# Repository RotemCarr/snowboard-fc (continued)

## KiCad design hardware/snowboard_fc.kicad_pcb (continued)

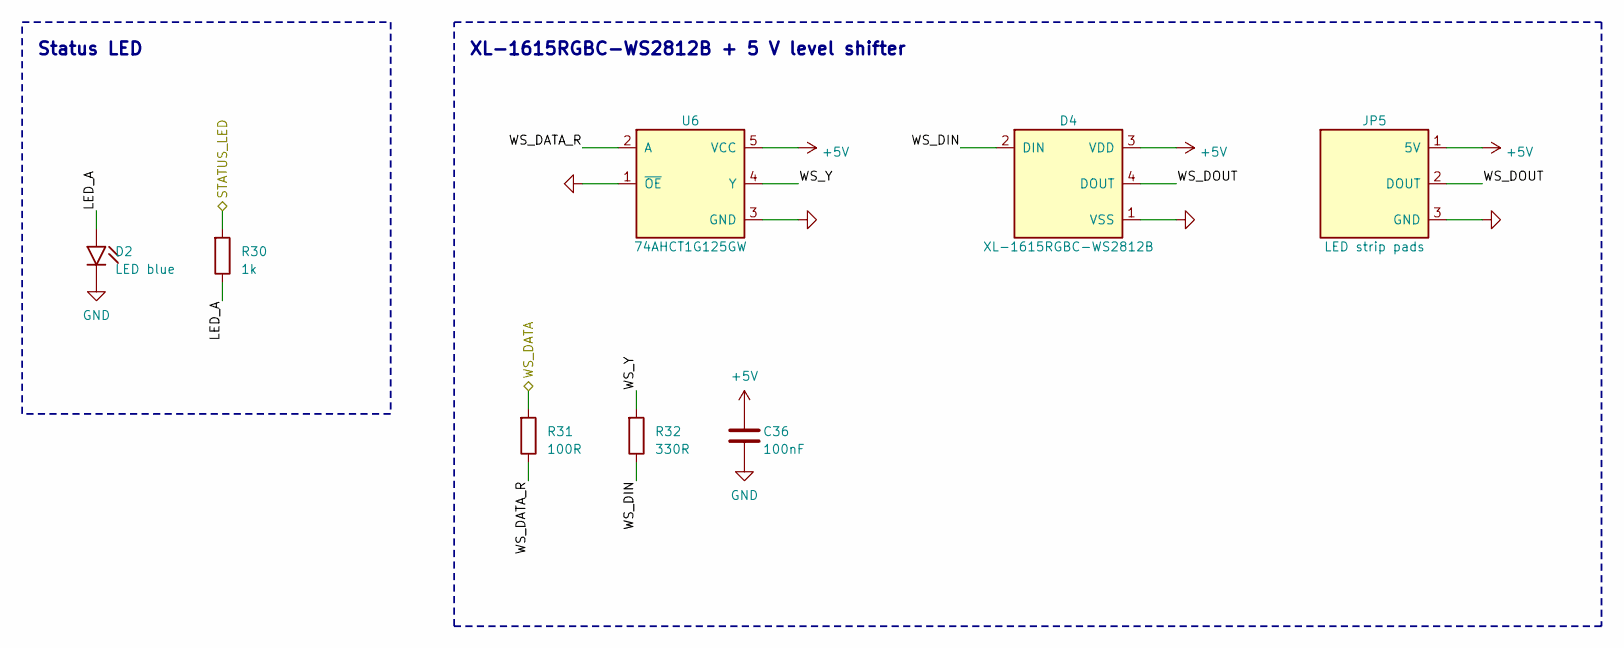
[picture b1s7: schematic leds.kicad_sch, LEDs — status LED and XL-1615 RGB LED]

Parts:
C36: 100nF; C_0402_1005Metric; LCSC C1525
D2: LED blue; LED_0603_1608Metric; LCSC C125096
D4: XL-1615RGBC-WS2812B; LED_XL-1615RGBC-WS2812B; MPN XL-1615RGBC-WS2812B (XINGLIGHT); LCSC C5349954
JP5: LED strip pads; PinHeader_1x03_P1.27mm_Vertical
R30: 1k; R_0402_1005Metric; LCSC C11702
R31: 100R; R_0402_1005Metric; LCSC C25076
R32: 330R; R_0402_1005Metric; LCSC C25104
U6: 74AHCT1G125GW; SOT-353_SC-70-5; MPN 74AHCT1G125GW (Nexperia); LCSC C52953352

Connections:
+5V: C36.1, D4.3 (VDD), JP5.1 (5V), U6.5 (VCC); also elsewhere on the board
/LEDs/LED_A: D2.2, R30.2
/LEDs/WS_DATA_R: R31.2, U6.2 (A)
/LEDs/WS_DIN: D4.2 (DIN), R32.2
/LEDs/WS_DOUT: D4.4 (DOUT), JP5.2 (DOUT)
/LEDs/WS_Y: R32.1, U6.4 (Y)
/STATUS_LED: R30.1; also elsewhere on the board
/WS_DATA: R31.1; also elsewhere on the board
GND: C36.2, D2.1, D4.1 (VSS), JP5.3 (GND), U6.1 (~OE), U6.3 (GND); also elsewhere on the board

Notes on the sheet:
Status LED
XL-1615RGBC-WS2812B + 5 V level shifter

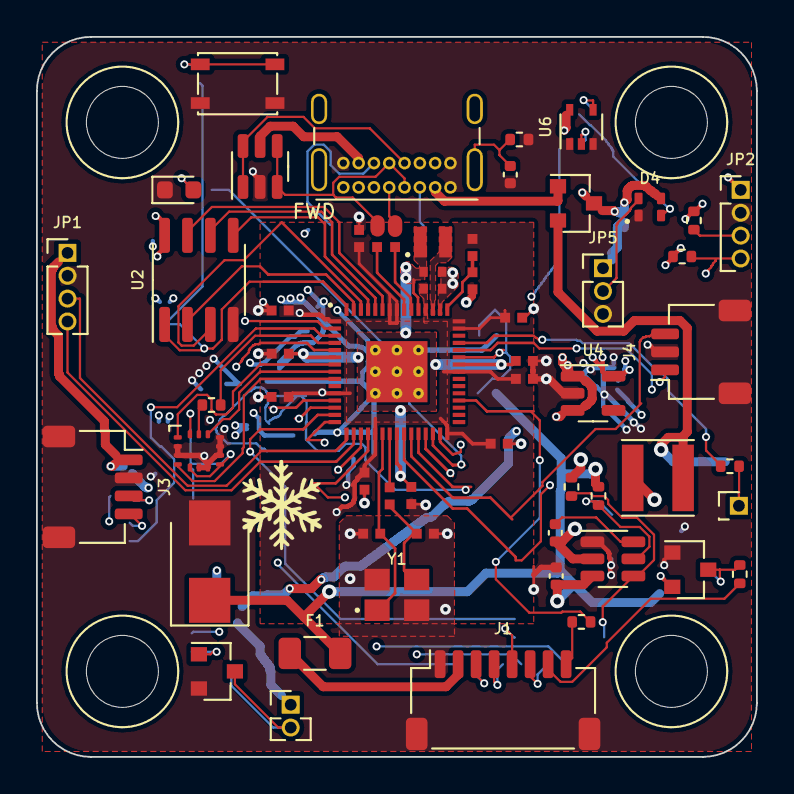
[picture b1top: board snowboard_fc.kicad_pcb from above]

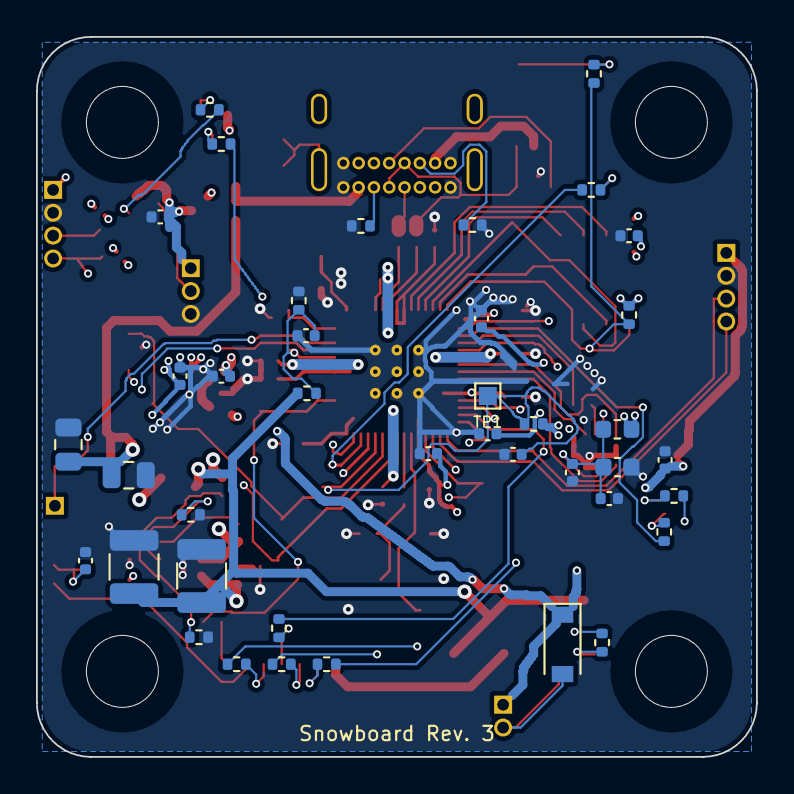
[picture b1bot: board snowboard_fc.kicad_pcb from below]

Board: 4 copper layers, 40.0 x 40.0 mm, 102 parts (40 on the bottom side), 74 nets.

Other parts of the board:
H1, H2, H3, H4: M3 grommet 4.0mm; MountingHole_4.0mm_Grommet

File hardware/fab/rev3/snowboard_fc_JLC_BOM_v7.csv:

Comment,Designator,Footprint,LCSC Part #
4.7uF 10V X5R,"C1,C4,C5",0402,C23733
100nF 16V X7R,"C2,C3,C6,C7,C8,C9,C10,C11,C12,C13,C14,C16,C17,C20,C24,C30,C33,C34,C35,C36",0402,C1525
1uF 25V X5R,"C15,C27,C28",0402,C52923
15pF 50V C0G,"C18,C19",0402,C1548
10uF 100V X7R,"C21,C22",1210,C5156756
100nF 50V X7R,C23,0402,C307331
22uF 25V X5R,"C25,C26",0805,C45783
2.2uF 16V X5R,C29,0603,C23630
10nF 50V X7R,C31,0402,C696350
4.7nF 50V X7R,C32,0402,C1538
BAT54C,D1,SOT-23,C22466350
LED blue 0603,D2,0603,C125096
SMBJ26A,D3,SMB,C3019963
XINGLIGHT XL-1615RGBC-WS2812B,D4,1615,C5349954
USBLC6-2SC6,D5,SOT-23-6,C7519
BAT54S,D6,SOT-23,C7420333
1N4148W,D7,SOD-123,C81598
F12F1 fuse 1A fast 1206 32V,F1,1206,C2924985
600R@100MHz ferrite,FB1,0603,C1002
JST SM08B-SRSS-TB(LF)(SN) 8-pin SH side entry,J1,SH-1.0mm-8P-RA,C160407
GCT USB4085-GF-A USB-C 2.0 (through-hole) - Global Sourcing,J2,USB-C THT,
JST SM04B-SRSS-TB(LF)(SN) 4-pin SH side entry,J3,SH-1.0mm-4P-RA,C160404
JST SM03B-SRSS-TB(LF)(SN) 3-pin SH side entry,J4,SH-1.0mm-3P-RA,C160403
10uH 4x4mm shielded,L1,4x4mm,C340371
AOTA-B201610S3R3-101-T 3.3uH (RP2350 recommended),L2,0806,C42411119
2N7002,Q1,SOT-23,C8545
33R 1% 0402,"R1,R10",0402,C25105
10k 1% 0402,"R2,R4,R22,R23,R28",0402,C25744
1k 1% 0402,"R3,R5,R20,R29,R30",0402,C11702
100k 1% 0402,"R6,R8,R21",0402,C25741
20k 1% 0402,R7,0402,C25765
13.3k 1% 0402,R9,0402,C122547
5.1k 1% 0402,"R11,R12",0402,C25905
1M 1% 0402,R13,0402,C26083
27R 1% 0402,"R14,R15",0402,C25100
100R 1% 0402,"R16,R17,R18,R19,R24,R25,R31",0402,C25076
4.7k 1% 0402,"R26,R27",0402,C25900
330R 1% 0402,R32,0402,C25104
C&K PTS810SJM250SMTRLFS tactile switch - Global Sourcing,SW1,SMD,
RP2350A,U1,QFN-60,C42411118
W25Q32JVSNIQ,U2,SOIC-8,C5355146
TPS54202DDCT,U3,SOT-23-6,C2070672
AP2112K-3.3TRG1,U4,SOT-23-5,C51118
ICM-42688-P,U5,LGA-14,C1850418
74AHCT1G125GW,U6,SOT-353,C52953352
ABM8-272-T3 12MHz 10pF (RP2350 recommended),Y1,3225,C20625731

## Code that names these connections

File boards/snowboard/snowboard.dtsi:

/*
 * Snowboard Rev 3 board-level devicetree.
 * Source: hardware/docs/pinmap.md, SNB-HW-001.
 *
 * TODO: flash partitions and retained RAM (RFC 0002 sections 8 and 9.4).
 * TODO: DShot on &pio0 once the custom binding exists.
 * TODO: CRSF receiver node on &uart0 once the driver exists.
 *
 * SPDX-License-Identifier: Apache-2.0
 */

#include <freq.h>

#include <zephyr/dt-bindings/adc/adc.h>
#include <zephyr/dt-bindings/i2c/i2c.h>
#include <zephyr/dt-bindings/led/led.h>
#include <zephyr/dt-bindings/sensor/icm42688.h>

#include "snowboard-pinctrl.dtsi"

/ {
	model = "Snowboard flight controller";
	compatible = "snowboard,snowboard-fc";

	chosen {
		zephyr,sram = &sram0;
		zephyr,flash = &flash0;
		zephyr,flash-controller = &qmi;
	};

	aliases {
		led0 = &status_led;
		led-strip = &rgb_led;
		buzzer = &buzzer;
		watchdog0 = &wdt0;
	};

	leds {
		compatible = "gpio-leds";

		/* D2, blue, through 1 kOhm */
		status_led: status_led {
			gpios = <&gpio0 17 GPIO_ACTIVE_HIGH>;
			label = "Status LED";
		};
	};

	buzzer {
		compatible = "gpio-leds";

		/* Low-side driver Q1; BZ+ on 5 V */
		buzzer: buzzer {
			gpios = <&gpio0 18 GPIO_ACTIVE_HIGH>;
			label = "Buzzer";
		};
	};

	/* VBAT = J1 pin 2 through R21 100k / R22 10k (divide by 11) */
	vbat: vbat {
		compatible = "voltage-divider";
		io-channels = <&adc 0>;
		output-ohms = <10000>;
		full-ohms = <110000>;
	};
};

/* W25Q32JVSNIQ, 4 MB. */
&flash0 {
	reg = <0x10000000 DT_SIZE_M(4)>;
};

/* CRSF receiver on J3 */
&uart0 {
	current-speed = <420000>;
	status = "okay";
	pinctrl-0 = <&uart0_default>;
	pinctrl-names = "default";
};

&gpio0 {
	status = "okay";
};

&spi0 {
	pinctrl-0 = <&spi0_default>;
	pinctrl-names = "default";
	clock-frequency = <DT_FREQ_M(24)>;
	cs-gpios = <&gpio0 5 GPIO_ACTIVE_LOW>;
	status = "okay";

	imu: icm42688@0 {
		compatible = "invensense,icm42688", "invensense,icm4268x";
		reg = <0>;
		spi-max-frequency = <DT_FREQ_M(24)>;
		/* INT1: push-pull, no pull-up on the board; driver default is active high */
		int-gpios = <&gpio0 6 GPIO_ACTIVE_HIGH>;
		gyro-pwr-mode = <ICM42688_DT_GYRO_LN>;
		gyro-fs = <ICM42688_DT_GYRO_FS_2000>;
		gyro-odr = <ICM42688_DT_GYRO_ODR_8000>;
		accel-pwr-mode = <ICM42688_DT_ACCEL_LN>;
		accel-fs = <ICM42688_DT_ACCEL_FS_16>;
		accel-odr = <ICM42688_DT_ACCEL_ODR_8000>;
	};
};

/* Aux I2C pads (JP2), nothing fitted */
&i2c1 {
	clock-frequency = <I2C_BITRATE_STANDARD>;
	pinctrl-0 = <&i2c1_default>;
	pinctrl-names = "default";
	status = "disabled";
};

&adc {
	pinctrl-0 = <&adc_default>;
	pinctrl-names = "default";
	#address-cells = <1>;
	#size-cells = <0>;
	status = "okay";

	/* VBAT_SENSE, GPIO26 */
	channel@0 {
		reg = <0>;
		zephyr,gain = "ADC_GAIN_1";
		zephyr,reference = "ADC_REF_INTERNAL";
		zephyr,acquisition-time = <ADC_ACQ_TIME_DEFAULT>;
		zephyr,resolution = <12>;
	};

	/* CUR_SENSE, GPIO27; ESC output 40 mV/A */
	channel@1 {
		reg = <1>;
		zephyr,gain = "ADC_GAIN_1";
		zephyr,reference = "ADC_REF_INTERNAL";
		zephyr,acquisition-time = <ADC_ACQ_TIME_DEFAULT>;
		zephyr,resolution = <12>;
	};

	/* RSSI pad, GPIO28 */
	channel@2 {
		reg = <2>;
		zephyr,gain = "ADC_GAIN_1";
		zephyr,reference = "ADC_REF_INTERNAL";
		zephyr,acquisition-time = <ADC_ACQ_TIME_DEFAULT>;
		zephyr,resolution = <12>;
	};
};

/* PIO0: DShot M1-M4 (GPIO8-11). Enabled with the DShot node. */
&pio0 {
	status = "disabled";
};

/* PIO1: RGB LED D4 via the 74AHCT1G125 level shifter */
&pio1 {
	status = "okay";

	pio-ws2812 {
		compatible = "worldsemi,ws2812-rpi_pico-pio";
		pinctrl-0 = <&pio1_default>;
		pinctrl-names = "default";
		bit-waveform = <3>, <3>, <4>;

		rgb_led: ws2812 {
			gpios = <&gpio0 16 GPIO_ACTIVE_HIGH>;
			chain-length = <1>;
			color-mapping = <LED_COLOR_ID_GREEN LED_COLOR_ID_RED LED_COLOR_ID_BLUE>;
			reset-delay = <300>;
			frequency = <800000>;
		};
	};
};

/* PIO2: aux UART on JP1 (GPIO12/13 have no free hardware UART) */
&pio2 {
	status = "okay";

	aux_uart: uart-aux {
		compatible = "raspberrypi,pico-uart-pio";
		pinctrl-0 = <&pio2_uart_aux_default>;
		pinctrl-names = "default";
		current-speed = <115200>;
	};
};

&timer0 {
	status = "okay";
};

&wdt0 {
	status = "okay";
};

&rng {
	status = "okay";
};

zephyr_udc0: &usbd {
	status = "okay";
};

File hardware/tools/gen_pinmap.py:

#!/usr/bin/env python3
"""Generate docs/pinmap.md from the schematic netlist.

Usage (from the KiCad project directory):
    python3 tools/gen_pinmap.py

Exports the netlist with kicad-cli, maps every RP2350A (U1) pin to its net,
and traces each GPIO through series parts to its far end (connector, pad or
IC). The peripheral column is the firmware's intended pin function, taken
from PERIPHERAL below. The script fails if a GPIO's net no longer matches
EXPECTED_NET, so a schematic change cannot silently desync the firmware DTS.
"""
import re, subprocess, sys, tempfile, pathlib

SCH = "snowboard_fc.kicad_sch"
OUT = pathlib.Path("docs/pinmap.md")
MCU = "U1"

# GPIO -> (expected net, intended peripheral, direction). Keep in sync with
# SNB-HW-001 section 7 and the board DTS.
EXPECTED = {
    0:  ("/RX_TX",      "UART0 TX",        "out"),
    1:  ("/RX_RX",      "UART0 RX",        "in"),
    2:  ("/IMU_SCK",    "SPI0 SCK",        "out"),
    3:  ("/IMU_MOSI",   "SPI0 TX",         "out"),
    4:  ("/IMU_MISO",   "SPI0 RX",         "in"),
    5:  ("/IMU_CS",     "GPIO (SPI0 CS)",  "out"),
    6:  ("/IMU_INT1",   "GPIO interrupt",  "in"),
    8:  ("/M1",         "PIO0 (DShot)",    "out"),
    9:  ("/M2",         "PIO0 (DShot)",    "out"),
    10: ("/M3",         "PIO0 (DShot)",    "out"),
    11: ("/M4",         "PIO0 (DShot)",    "out"),
    12: ("/AUX_TX",     "PIO UART TX",     "out"),
    13: ("/AUX_RX",     "PIO UART RX",     "in"),
    14: ("/I2C_SDA",    "I2C1 SDA",        "bidir"),
    15: ("/I2C_SCL",    "I2C1 SCL",        "out"),
    16: ("/WS_DATA",    "PIO1 (WS2812)",   "out"),
    17: ("/STATUS_LED", "GPIO",            "out"),
    18: ("/BUZZ",       "GPIO",            "out"),
    22: ("/ESC_TEL",    "PIO UART RX",     "in"),
    26: ("/VBAT_SENSE", "ADC0",            "in"),
    27: ("/CUR_SENSE",  "ADC1",            "in"),
    28: ("/RSSI",       "ADC2",            "in"),
}
SERIES = ("R", "L", "FB")      # parts traced through to the far end
RAILS = {"GND", "+3V3", "+5V"}


def export_netlist():
    tmp = pathlib.Path(tempfile.mkdtemp()) / "pinmap.net"
    subprocess.run(["kicad-cli", "sch", "export", "netlist", "--format",
                    "kicadsexpr", "-o", str(tmp), SCH],
                   check=True, capture_output=True)
    return tmp.read_text()


def parse(t):
    values = dict(re.findall(r'\(comp \(ref "([^"]+)"\)\s*\(value "([^"]*)"\)', t))
    nets, net_of, func_of = {}, {}, {}
    for m in re.finditer(r'\(net \(code "?\d+"?\) \(name "([^"]*)"\)(.*?)(?=\(net \(code|\Z)', t, re.S):
        nodes = re.findall(r'\(node \(ref "([^"]+)"\) \(pin "([^"]+)"\)(?: \(pinfunction "([^"]*)"\))?', m.group(2))
        nets[m.group(1)] = nodes
        for r, p, f in nodes:
            net_of[(r, p)] = m.group(1)
            func_of[(r, p)] = f
    return values, nets, net_of, func_of


def pin_order(label):
    m = re.search(r"\((\d+)\)$", label)
    return int(m.group(1)) if m else 999


def fmt(ref, pin, func, values):
    label = f"{ref}.{pin}" + (f" ({func})" if func else "")
    return f"{label} {values.get(ref, '')}".strip()


def trace(net, frm, values, nets, net_of):
    """Describe where a net goes, following 2-pin series parts once."""
    out = []
    for r, p, f in nets[net]:
        if (r, p) == frm:
            continue
        if r.startswith(SERIES):
            other = "2" if p == "1" else "1"
            far = net_of.get((r, other))
            part = f"{r} {values.get(r, '')}"
            ends = [(a, b, c) for a, b, c in nets[far] if (a, b) != (r, other)]
            if far in RAILS or len(ends) > 4:
                out.append(f"{part} to `{far.lstrip('/')}`")
            else:
                out.append(f"{part} → " + ", ".join(fmt(a, b, c, values) for a, b, c in ends))
        elif r[0] == "C":
            other = "2" if p == "1" else "1"
            out.append(f"{r} {values.get(r, '')} to `{net_of.get((r, other)).lstrip('/')}`")
        elif r == MCU:
            continue
        else:
            out.append(fmt(r, p, f, values))
    return "; ".join(out)


def main():
    values, nets, net_of, func_of = parse(export_netlist())
    pins = {p: (n, func_of[(r, p)]) for (r, p), n in net_of.items() if r == MCU}
    gpio_pin = {}
    for p, (n, f) in pins.items():
        m = re.match(r"GPIO(\d+)", f or "")
        if m:
            gpio_pin[int(m.group(1))] = p

    errors, rows = [], []
    for g in range(30):
        p = gpio_pin[g]
        net, _ = pins[p]
        if net.startswith("unconnected"):
            if g in EXPECTED:
                errors.append(f"GPIO{g}: expected {EXPECTED[g][0]}, now unconnected")
            rows.append(f"| {g} | {p} | — | not connected | — | — |")
            continue
        exp = EXPECTED.get(g)
        if not exp or exp[0] != net:
            errors.append(f"GPIO{g}: netlist says {net}, EXPECTED says {exp[0] if exp else 'nothing'}")
            continue
        rows.append(f"| {g} | {p} | `{net.lstrip('/')}` | {exp[1]} | {exp[2]} | "
                    f"{trace(net, (MCU, p), values, nets, net_of)} |")
    if errors:
        sys.exit("pin map out of date:\n  " + "\n  ".join(errors))

    special = []
    for p in sorted(pins, key=lambda x: (not x.isdigit(), int(x) if x.isdigit() else 0)):
        n, f = pins[p]
        if f and not f.startswith("GPIO") and n not in RAILS and n not in ("GND", "/MCU/DVDD"):
            special.append(f"| {p} | {f.replace('~{CS}', 'CS')} | `{n.lstrip('/')}` | "
                           f"{trace(n, (MCU, p), values, nets, net_of)} |")
    supplies = {}
    for p, (n, f) in pins.items():
        if n in RAILS or n == "/MCU/DVDD":
            supplies.setdefault(n.lstrip("/"), []).append(f"{f} ({p})")

    md = [
        "# Snowboard Rev 3 pin map",
        "",
        "Generated by `tools/gen_pinmap.py` from `snowboard_fc.kicad_sch`. Do not edit by hand:",
        "change the schematic (and `EXPECTED` in the script if a pin moves), then regenerate.",
        "Authoritative for the board DTS and pinctrl. Spec: SNB-HW-001 section 7.",
        "",
        "## GPIO",
        "",
        "| GPIO | Pin | Net | Peripheral | Dir | Connects to |",
        "| --- | --- | --- | --- | --- | --- |",
        *rows,
        "",
        "Notes:",
        "",
        "- GPIO12/13 offer only UART0 (already used by the receiver on GPIO0/1) and GPIO22 offers only",
        "  UART1 TX, so the aux UART and ESC telemetry use PIO UARTs (SNB-HW-001 L-07).",
        "- ADC inputs are limited to GPIO26–29 on the RP2350A.",
        "- RP2350 erratum E9: internal pull-downs are not used on any input.",
        "",
        "## Dedicated pins",
        "",
        "| Pin | Function | Net | Connects to |",
        "| --- | --- | --- | --- |",
        *special,
        "",
        "## Supply pins",
        "",
        "| Net | Pins |",
        "| --- | --- |",
        *[f"| `{n}` | {', '.join(sorted(v, key=pin_order))} |" for n, v in sorted(supplies.items())],
        "",
    ]
    OUT.parent.mkdir(exist_ok=True)
    OUT.write_text("\n".join(md))
    print(f"wrote {OUT}: {len(rows)} GPIO rows, {len(special)} dedicated pins")


if __name__ == "__main__":
    main()

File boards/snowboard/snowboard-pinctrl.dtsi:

/*
 * Snowboard Rev 3 pin assignments.
 * Source: hardware/docs/pinmap.md (generated from the schematic),
 * SNB-HW-001 section 7.
 *
 * Plain GPIOs have no group here; they are set by *-gpios properties
 * in snowboard.dtsi: GPIO5 IMU CS, GPIO6 IMU INT1, GPIO17 status LED,
 * GPIO18 buzzer.
 * Not yet assigned: GPIO22 ESC telemetry (needs an RX-only PIO UART).
 *
 * SPDX-License-Identifier: Apache-2.0
 */

#include <zephyr/dt-bindings/pinctrl/rpi-pico-rp2350a-pinctrl.h>

&pinctrl {
	/* CRSF receiver, J3 */
	uart0_default: uart0_default {
		group1 {
			pinmux = <UART0_TX_P0>;
		};

		group2 {
			pinmux = <UART0_RX_P1>;
			input-enable;
		};
	};

	/* IMU. CS is GPIO5 via cs-gpios, not the SPI block's CSn. */
	spi0_default: spi0_default {
		group1 {
			pinmux = <SPI0_SCK_P2>, <SPI0_TX_P3>;
		};

		group2 {
			pinmux = <SPI0_RX_P4>;
			input-enable;
		};
	};

	/* Aux I2C pads (JP2). External 4.7 kOhm pull-ups on the board. */
	i2c1_default: i2c1_default {
		group1 {
			pinmux = <I2C1_SDA_P14>, <I2C1_SCL_P15>;
			input-enable;
			input-schmitt-enable;
		};
	};

	/* VBAT_SENSE, CUR_SENSE, RSSI. */
	adc_default: adc_default {
		group1 {
			pinmux = <ADC_CH0_P26>, <ADC_CH1_P27>, <ADC_CH2_P28>;
		};
	};

	/* DShot M1-M4, consecutive pins on one PIO block */
	pio0_default: pio0_default {
		group1 {
			pinmux = <PIO0_P8>, <PIO0_P9>, <PIO0_P10>, <PIO0_P11>;
		};
	};

	/* WS2812 data to the 5 V level shifter */
	pio1_default: pio1_default {
		group1 {
			pinmux = <PIO1_P16>;
		};
	};

	/* Aux UART pads (JP1); GPIO12/13 have no free hardware UART */
	pio2_uart_aux_default: pio2_uart_aux_default {
		tx_pins {
			pinmux = <PIO2_P12>;
		};

		rx_pins {
			pinmux = <PIO2_P13>;
			input-enable;
			bias-pull-up;
		};
	};
};
